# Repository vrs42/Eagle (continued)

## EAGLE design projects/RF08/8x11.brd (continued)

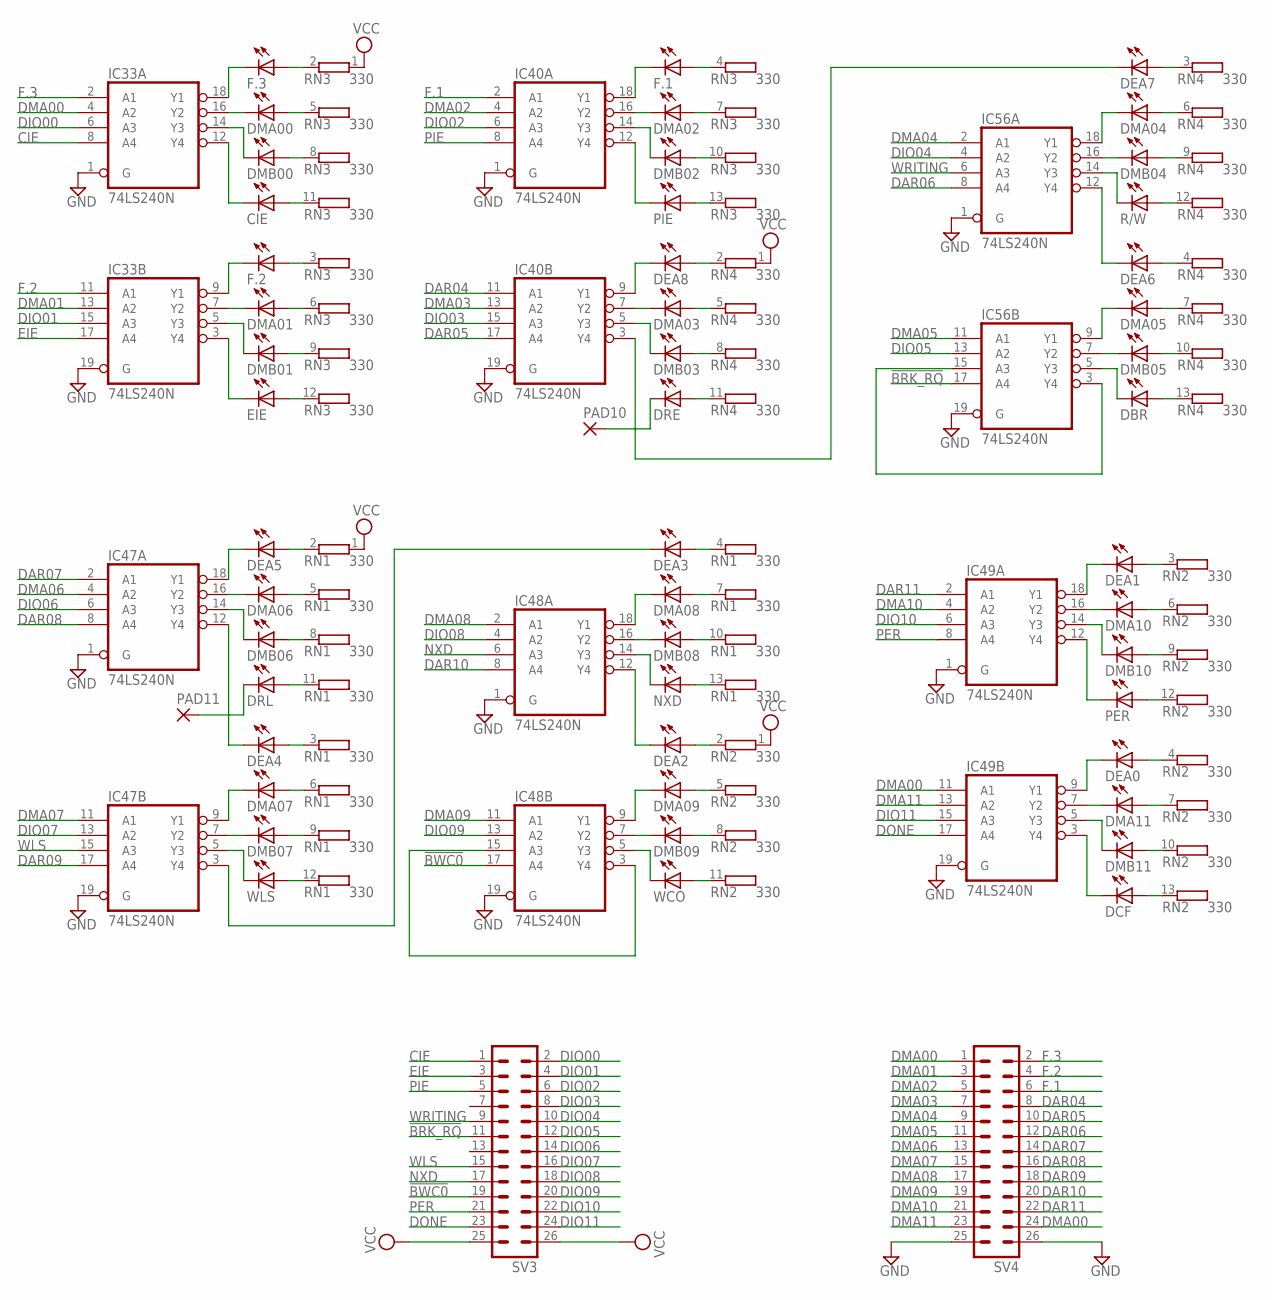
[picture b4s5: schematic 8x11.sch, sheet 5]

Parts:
CIE: LED5MM
DBR: LED5MM
DCF: LED5MM
DEA0, DEA1, DEA2, DEA3, DEA4, DEA5, DEA6, DEA7, DEA8: LED5MM
DMA00, DMA01, DMA02, DMA03, DMA04, DMA05, DMA06, DMA07, DMA08, DMA09, DMA10, DMA11: LED5MM
DMB00, DMB01, DMB02, DMB03, DMB04, DMB05, DMB06, DMB07, DMB08, DMB09, DMB10, DMB11: LED5MM
DRE: LED5MM
DRL: LED5MM
EIE: LED5MM
F.1, F.2, F.3: LED5MM
IC33, IC40, IC47, IC48, IC49, IC56: 74LS240N; DIL20
NXD: LED5MM
PAD10, PAD11: 1,6/0,8
PER: LED5MM
PIE: LED5MM
R/W: LED5MM
RN1, RN2, RN3, RN4: 330; SIL13
SV3, SV4: MA13-2
WCO: LED5MM
WLS: LED5MM

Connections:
!BRK_RQ: IC56.17 (A4), SV3.11; also elsewhere on the board
!BWC0: IC48.17 (A4), SV3.19; also elsewhere on the board
CIE: IC33.8 (A4), SV3.1; also elsewhere on the board
DAR04: IC40.11 (A1), SV4.8; also elsewhere on the board
DAR05: IC40.17 (A4), SV4.10; also elsewhere on the board
DAR06: IC56.8 (A4), SV4.12; also elsewhere on the board
DAR07: IC47.2 (A1), SV4.14; also elsewhere on the board
DAR08: IC47.8 (A4), SV4.16; also elsewhere on the board
DAR09: IC47.17 (A4), SV4.18; also elsewhere on the board
DAR10: IC48.8 (A4), SV4.20; also elsewhere on the board
DAR11: IC49.2 (A1), SV4.22; also elsewhere on the board
DIO00: IC33.6 (A3), SV3.2; also elsewhere on the board
DIO01: IC33.15 (A3), SV3.4; also elsewhere on the board
DIO02: IC40.6 (A3), SV3.6; also elsewhere on the board
DIO03: IC40.15 (A3), SV3.8; also elsewhere on the board
DIO04: IC56.4 (A2), SV3.10; also elsewhere on the board
DIO05: IC56.13 (A2), SV3.12; also elsewhere on the board
DIO06: IC47.6 (A3), SV3.14; also elsewhere on the board
DIO07: IC47.13 (A2), SV3.16; also elsewhere on the board
DIO08: IC48.4 (A2), SV3.18; also elsewhere on the board
DIO09: IC48.13 (A2), SV3.20; also elsewhere on the board
DIO10: IC49.6 (A3), SV3.22; also elsewhere on the board
DIO11: IC49.15 (A3), SV3.24; also elsewhere on the board
DMA00: IC33.4 (A2), IC49.11 (A1), SV4.1, SV4.24; also elsewhere on the board
DMA01: IC33.13 (A2), SV4.3; also elsewhere on the board
DMA02: IC40.4 (A2), SV4.5; also elsewhere on the board
DMA03: IC40.13 (A2), SV4.7; also elsewhere on the board
DMA04: IC56.2 (A1), SV4.9; also elsewhere on the board
DMA05: IC56.11 (A1), SV4.11; also elsewhere on the board
DMA06: IC47.4 (A2), SV4.13; also elsewhere on the board
DMA07: IC47.11 (A1), SV4.15; also elsewhere on the board
DMA08: IC48.2 (A1), SV4.17; also elsewhere on the board
DMA09: IC48.11 (A1), SV4.19; also elsewhere on the board
DMA10: IC49.4 (A2), SV4.21; also elsewhere on the board
DMA11: IC49.13 (A2), SV4.23; also elsewhere on the board
DONE: IC49.17 (A4), SV3.23; also elsewhere on the board
EIE: IC33.17 (A4), SV3.3; also elsewhere on the board
F.1: IC40.2 (A1), SV4.6; also elsewhere on the board
F.2: IC33.11 (A1), SV4.4; also elsewhere on the board
F.3: IC33.2 (A1), SV4.2; also elsewhere on the board
GND: IC33.1 (G), IC33.10 (GND), IC33.19 (G), IC40.1 (G), IC40.10 (GND), IC40.19 (G), IC47.1 (G), IC47.10 (GND), IC47.19 (G), IC48.1 (G), IC48.10 (GND), IC48.19 (G), IC49.1 (G), IC49.10 (GND), IC49.19 (G), IC56.1 (G), IC56.10 (GND), IC56.19 (G), SV4.25, SV4.26; also elsewhere on the board
unnamed: F.3.A, RN3.2
unnamed: F.2.A, RN3.3 (2)
unnamed: F.1.A, RN3.4 (2)
unnamed: DEA8.A, RN4.2
unnamed: DEA2.A, RN2.2
unnamed: DEA1.A, RN2.3 (2)
unnamed: DEA5.A, RN1.2
unnamed: DEA4.A, RN1.3 (2)
unnamed: DEA3.A, RN1.4 (2)
unnamed: DEA0.A, RN2.4 (2)
unnamed: DMA09.A, RN2.5 (2)
unnamed: DMA10.A, RN2.6 (2)
unnamed: DMA00.A, RN3.5 (2)
unnamed: DMA01.A, RN3.6 (2)
unnamed: DMA02.A, RN3.7 (2)
unnamed: DEA7.A, RN4.3 (2)
unnamed: DEA6.A, RN4.4 (2)
unnamed: DMA03.A, RN4.5 (2)
unnamed: DMA07.A, RN1.6 (2)
unnamed: DMA06.A, RN1.5 (2)
unnamed: DMA08.A, RN1.7 (2)
unnamed: DMA11.A, RN2.7 (2)
unnamed: DMB09.A, RN2.8 (2)
unnamed: DMB10.A, RN2.9 (2)
unnamed: PIE.A, RN3.13 (2)
unnamed: EIE.A, RN3.12 (2)
unnamed: CIE.A, RN3.11 (2)
unnamed: DMA04.A, RN4.6 (2)
unnamed: DMA05.A, RN4.7 (2)
unnamed: DMB03.A, RN4.8 (2)
unnamed: DMB06.A, RN1.8 (2)
unnamed: DMB07.A, RN1.9 (2)
unnamed: DMB08.A, RN1.10 (2)
unnamed: DMB11.A, RN2.10 (2)
unnamed: RN2.11 (2), WCO.A
unnamed: PER.A, RN2.12 (2)
unnamed: DMB02.A, RN3.10 (2)
unnamed: DMB01.A, RN3.9 (2)
unnamed: DMB00.A, RN3.8 (2)
unnamed: DRE.A, RN4.11 (2)
unnamed: R/W.A, RN4.12 (2)
unnamed: DBR.A, RN4.13 (2)
unnamed: DRL.A, RN1.11 (2)
unnamed: RN1.12 (2), WLS.A
unnamed: NXD.A, RN1.13 (2)
unnamed: DCF.A, RN2.13 (2)
unnamed: DMA09.K (C), IC48.9 (Y1)
unnamed: DMB09.K (C), IC48.7 (Y2)
unnamed: F.3.K (C), IC33.18 (Y1)
unnamed: DMA00.K (C), IC33.16 (Y2)
unnamed: CIE.K (C), IC33.12 (Y4)
unnamed: DMB00.K (C), IC33.14 (Y3)
unnamed: DMA01.K (C), IC33.7 (Y2)
unnamed: F.2.K (C), IC33.9 (Y1)
unnamed: DMB01.K (C), IC33.5 (Y3)
unnamed: EIE.K (C), IC33.3 (Y4)
unnamed: F.1.K (C), IC40.18 (Y1)
unnamed: DMA02.K (C), IC40.16 (Y2)
unnamed: DMB02.K (C), IC40.14 (Y3)
unnamed: IC40.12 (Y4), PIE.K (C)
unnamed: DMB03.K (C), IC40.5 (Y3)
unnamed: DMA03.K (C), IC40.7 (Y2)
unnamed: DEA8.K (C), IC40.9 (Y1)
unnamed: DEA7.K (C), IC40.3 (Y4)
unnamed: DMA04.K (C), IC56.18 (Y1)
unnamed: DMB04.K (C), IC56.16 (Y2)
unnamed: IC56.14 (Y3), R/W.K (C)
unnamed: DMB05.K (C), IC56.7 (Y2)
unnamed: DEA6.K (C), IC56.12 (Y4)
unnamed: DBR.K (C), IC56.5 (Y3)
unnamed: DMA06.K (C), IC47.16 (Y2)
unnamed: DEA4.K (C), IC47.12 (Y4)
unnamed: DMB07.K (C), IC47.7 (Y2)
unnamed: DEA5.K (C), IC47.18 (Y1)
unnamed: DMA07.K (C), IC47.9 (Y1)
unnamed: IC47.5 (Y3), WLS.K (C)
unnamed: DMB06.K (C), IC47.14 (Y3)
unnamed: DEA3.K (C), IC47.3 (Y4)
unnamed: DMA08.K (C), IC48.18 (Y1)
unnamed: DMB08.K (C), IC48.16 (Y2)
unnamed: IC48.14 (Y3), NXD.K (C)
unnamed: IC48.5 (Y3), WCO.K (C)
unnamed: IC49.12 (Y4), PER.K (C)
unnamed: DMB10.K (C), IC49.14 (Y3)
unnamed: DEA2.K (C), IC48.12 (Y4)
unnamed: DMA10.K (C), IC49.16 (Y2)
unnamed: DEA1.K (C), IC49.18 (Y1)
unnamed: IC48.3 (Y4), IC48.15 (A3)
unnamed: DMA11.K (C), IC49.7 (Y2)
unnamed: DEA0.K (C), IC49.9 (Y1)
unnamed: DMB11.K (C), IC49.5 (Y3)
unnamed: DCF.K (C), IC49.3 (Y4)
unnamed: DRE.K (C), PAD10.1
unnamed: DRL.K (C), PAD11.1
unnamed: DMA05.K (C), IC56.9 (Y1)
unnamed: DMB04.A, RN4.9 (2)
unnamed: DMB05.A, RN4.10 (2)
unnamed: IC56.3 (Y4), IC56.15 (A3)
NXD: IC48.6 (A3), SV3.17; also elsewhere on the board
PER: IC49.8 (A4), SV3.21; also elsewhere on the board
PIE: IC40.8 (A4), SV3.5; also elsewhere on the board
VCC: IC33.20 (VCC), IC40.20 (VCC), IC47.20 (VCC), IC48.20 (VCC), IC49.20 (VCC), IC56.20 (VCC), RN1.1, RN2.1, RN3.1, RN4.1, SV3.25, SV3.26; also elsewhere on the board
WLS: IC47.15 (A3), SV3.15; also elsewhere on the board
WRITING: IC56.6 (A3), SV3.9; also elsewhere on the board

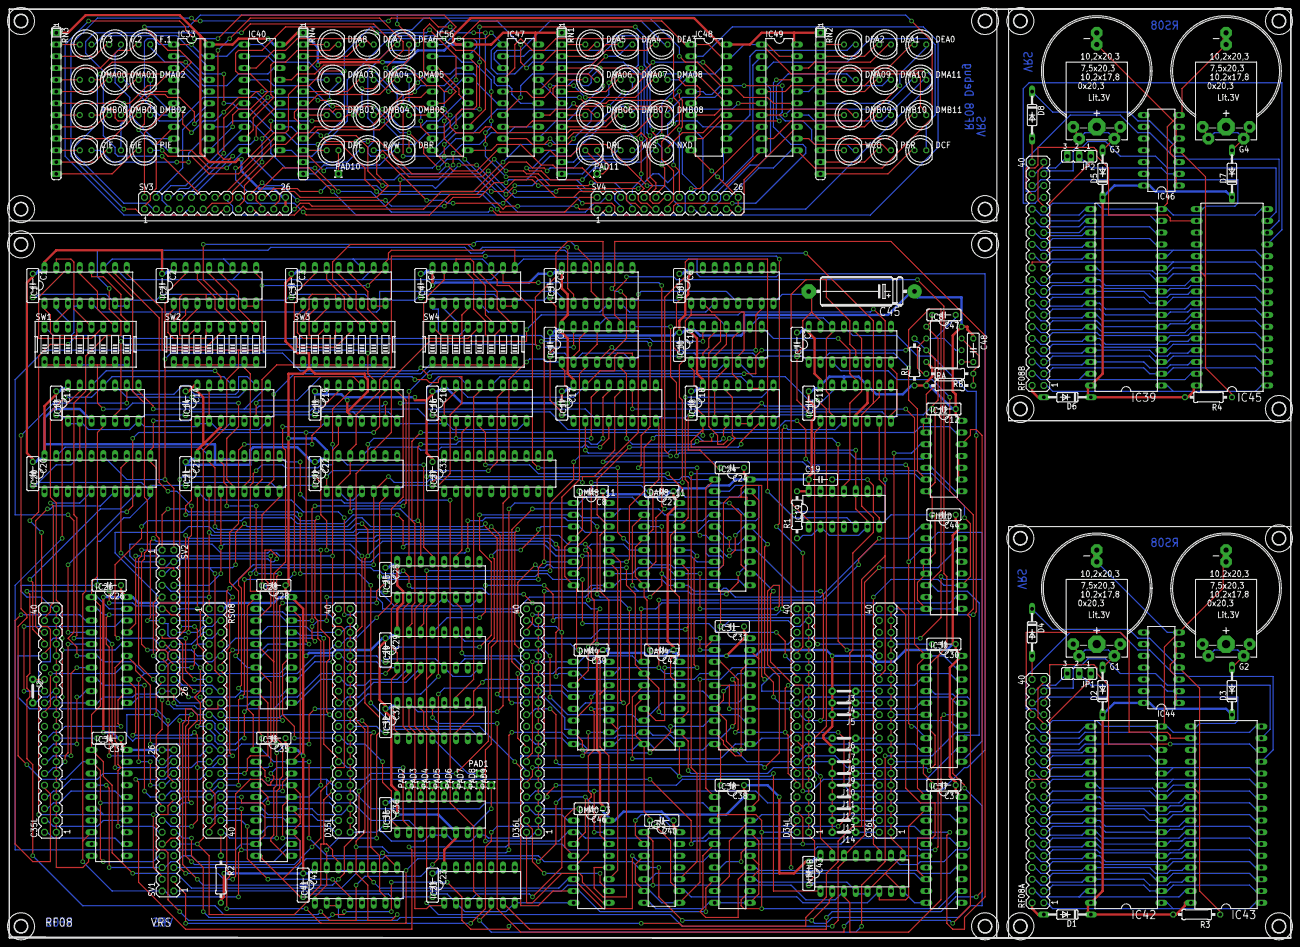
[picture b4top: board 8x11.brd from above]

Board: 2 copper layers, 276.9 x 200.7 mm, 236 parts (0 on the bottom side), 335 nets.

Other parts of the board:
U$1, U$2, U$3, U$4, U$5, U$6, U$7, U$8, U$9, U$10, U$11, U$12, U$13, U$14, U$16, U$17: 2,8
U$18: SIERRA-PROTO

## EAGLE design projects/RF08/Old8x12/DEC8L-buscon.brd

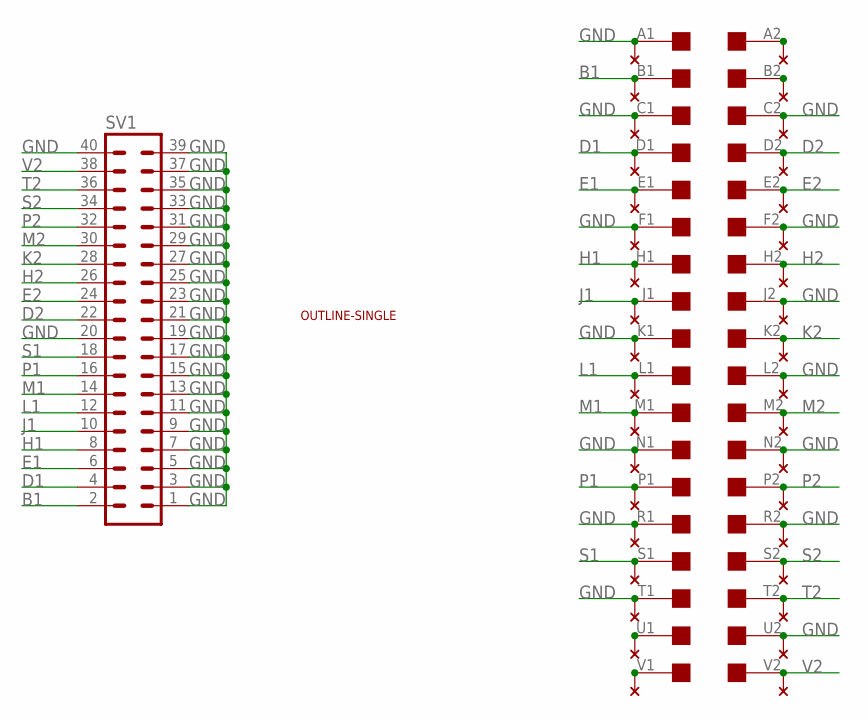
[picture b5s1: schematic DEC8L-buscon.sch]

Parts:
EDGE1: EDGE-2CONNECTOR; EDGE-CON2
SV1: MA20-2
U$4: OUTLINE-SINGLE; SINGLE
U$5: THRU-HOLE2; THRU-HOLEB

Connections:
B1: EDGE1.B1, SV1.2, U$5.B1
D1: EDGE1.D1, SV1.4, U$5.D1
D2: EDGE1.D2, SV1.22, U$5.D2
E1: EDGE1.E1, SV1.6, U$5.E1
E2: EDGE1.E2, SV1.24, U$5.E2
GND: EDGE1.A1, EDGE1.C1, EDGE1.C2, EDGE1.F1, EDGE1.F2, EDGE1.J2, EDGE1.K1, EDGE1.L2, EDGE1.N1, EDGE1.N2, EDGE1.R1, EDGE1.R2, EDGE1.T1, EDGE1.U2, SV1.1, SV1.3, SV1.5, SV1.7, SV1.9, SV1.11, SV1.13, SV1.15, SV1.17, SV1.19, SV1.20, SV1.21, SV1.23, SV1.25, SV1.27, SV1.29, SV1.31, SV1.33, SV1.35, SV1.37, SV1.39, SV1.40, U$5.A1, U$5.C1, U$5.C2, U$5.F1, U$5.F2, U$5.J2, U$5.K1, U$5.L2, U$5.N1, U$5.N2, U$5.R1, U$5.R2, U$5.T1, U$5.U2
H1: EDGE1.H1, SV1.8, U$5.H1
H2: EDGE1.H2, SV1.26, U$5.H2
J1: EDGE1.J1, SV1.10, U$5.J1
K2: EDGE1.K2, SV1.28, U$5.K2
L1: EDGE1.L1, SV1.12, U$5.L1
M1: EDGE1.M1, SV1.14, U$5.M1
M2: EDGE1.M2, SV1.30, U$5.M2
unnamed: EDGE1.B2, U$5.B2
unnamed: EDGE1.A2, U$5.A2
unnamed: EDGE1.U1, U$5.U1
unnamed: EDGE1.V1, U$5.V1
P1: EDGE1.P1, SV1.16, U$5.P1
P2: EDGE1.P2, SV1.32, U$5.P2
S1: EDGE1.S1, SV1.18, U$5.S1
S2: EDGE1.S2, SV1.34, U$5.S2
T2: EDGE1.T2, SV1.36, U$5.T2
V2: EDGE1.V2, SV1.38, U$5.V2

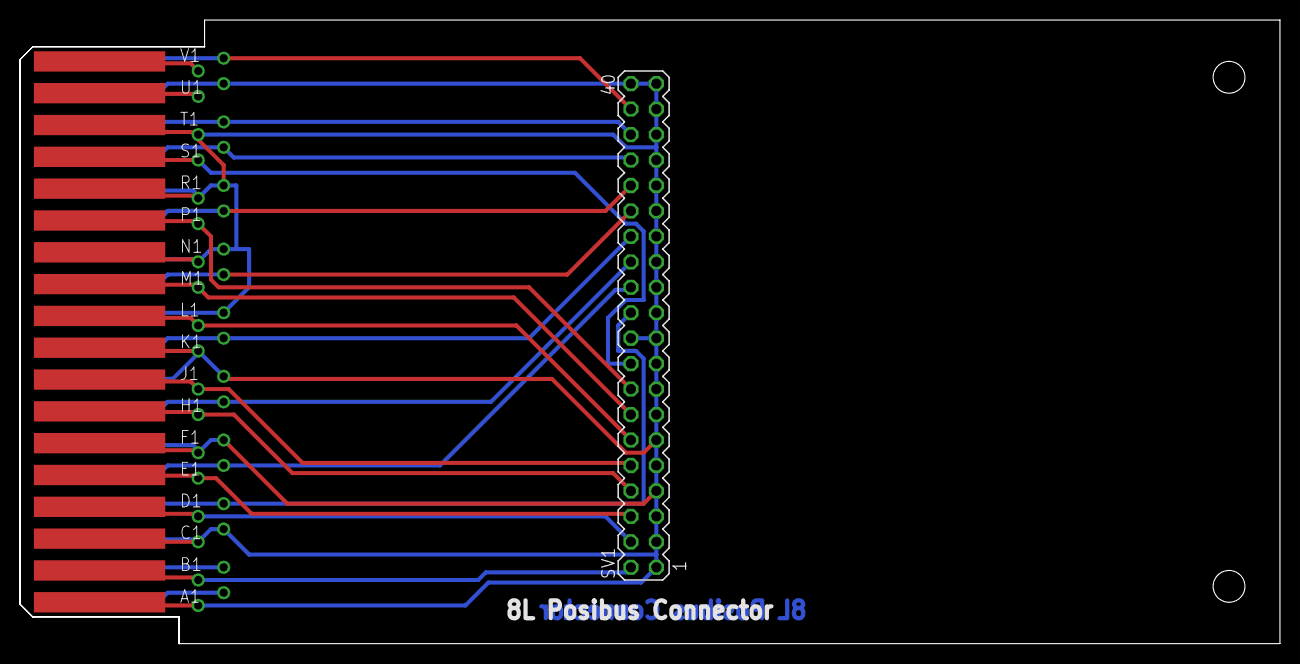
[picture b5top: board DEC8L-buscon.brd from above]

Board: 2 copper layers, 125.7 x 62.2 mm, 4 parts (0 on the bottom side), 23 nets.

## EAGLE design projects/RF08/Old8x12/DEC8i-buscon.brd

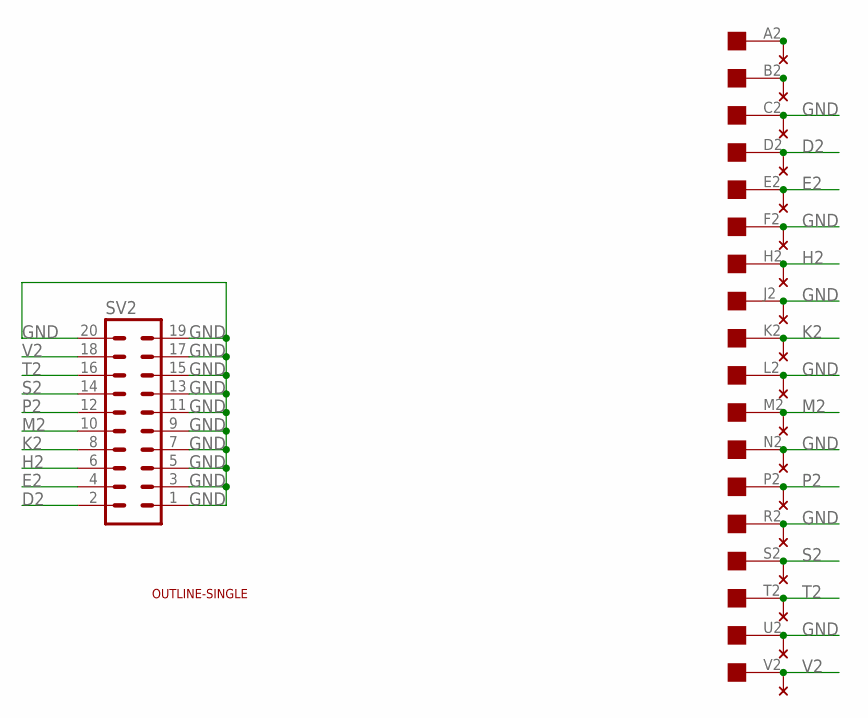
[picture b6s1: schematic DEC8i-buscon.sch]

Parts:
SV2: MA10-2
U$4: EDGE-1; EDGE-CON1
U$5: THRU-HOLE1
U$6: OUTLINE-SINGLE; SINGLE

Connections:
D2: SV2.2, U$4.D2, U$5.D2
E2: SV2.4, U$4.E2, U$5.E2
GND: SV2.1, SV2.3, SV2.5, SV2.7, SV2.9, SV2.11, SV2.13, SV2.15, SV2.17, SV2.19, SV2.20, U$4.C2, U$4.F2, U$4.J2, U$4.L2, U$4.N2, U$4.R2, U$4.U2, U$5.C2, U$5.F2, U$5.J2, U$5.L2, U$5.N2, U$5.R2, U$5.U2
H2: SV2.6, U$4.H2, U$5.H2
K2: SV2.8, U$4.K2, U$5.K2
M2: SV2.10, U$4.M2, U$5.M2
unnamed: U$4.B2, U$5.B2
unnamed: U$4.A2, U$5.A2
P2: SV2.12, U$4.P2, U$5.P2
S2: SV2.14, U$4.S2, U$5.S2
T2: SV2.16, U$4.T2, U$5.T2
V2: SV2.18, U$4.V2, U$5.V2

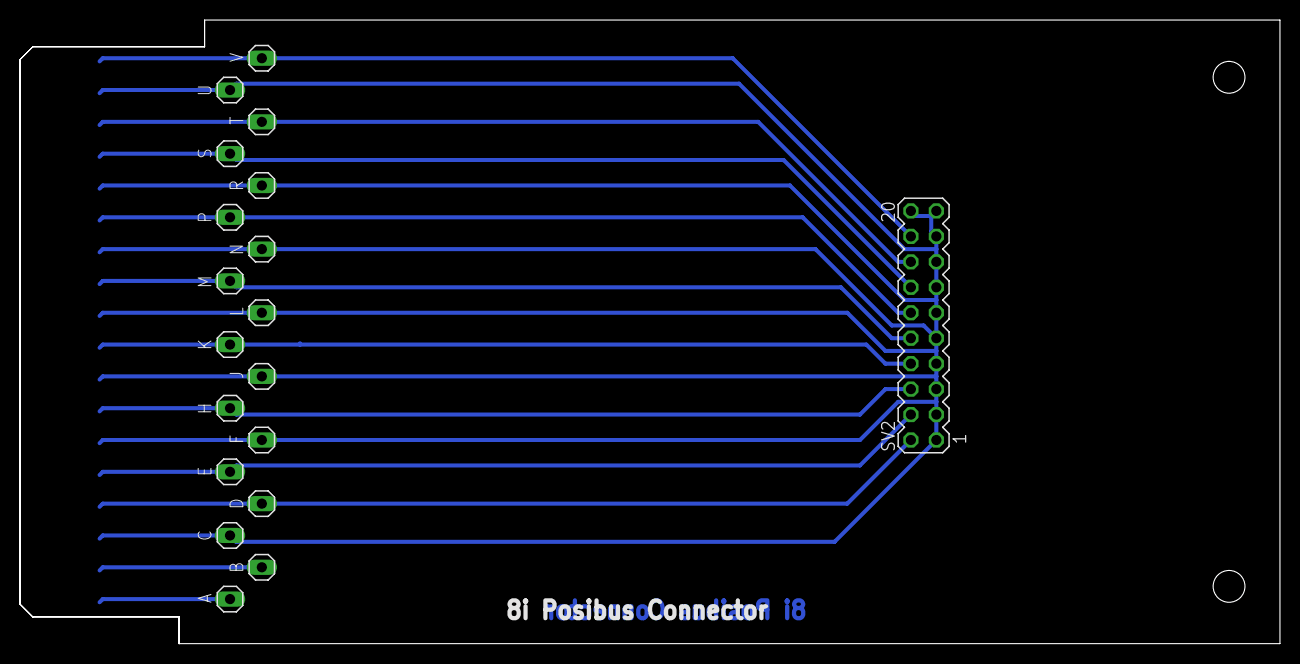
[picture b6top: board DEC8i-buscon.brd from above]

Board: 2 copper layers, 125.7 x 62.2 mm, 4 parts (0 on the bottom side), 12 nets.

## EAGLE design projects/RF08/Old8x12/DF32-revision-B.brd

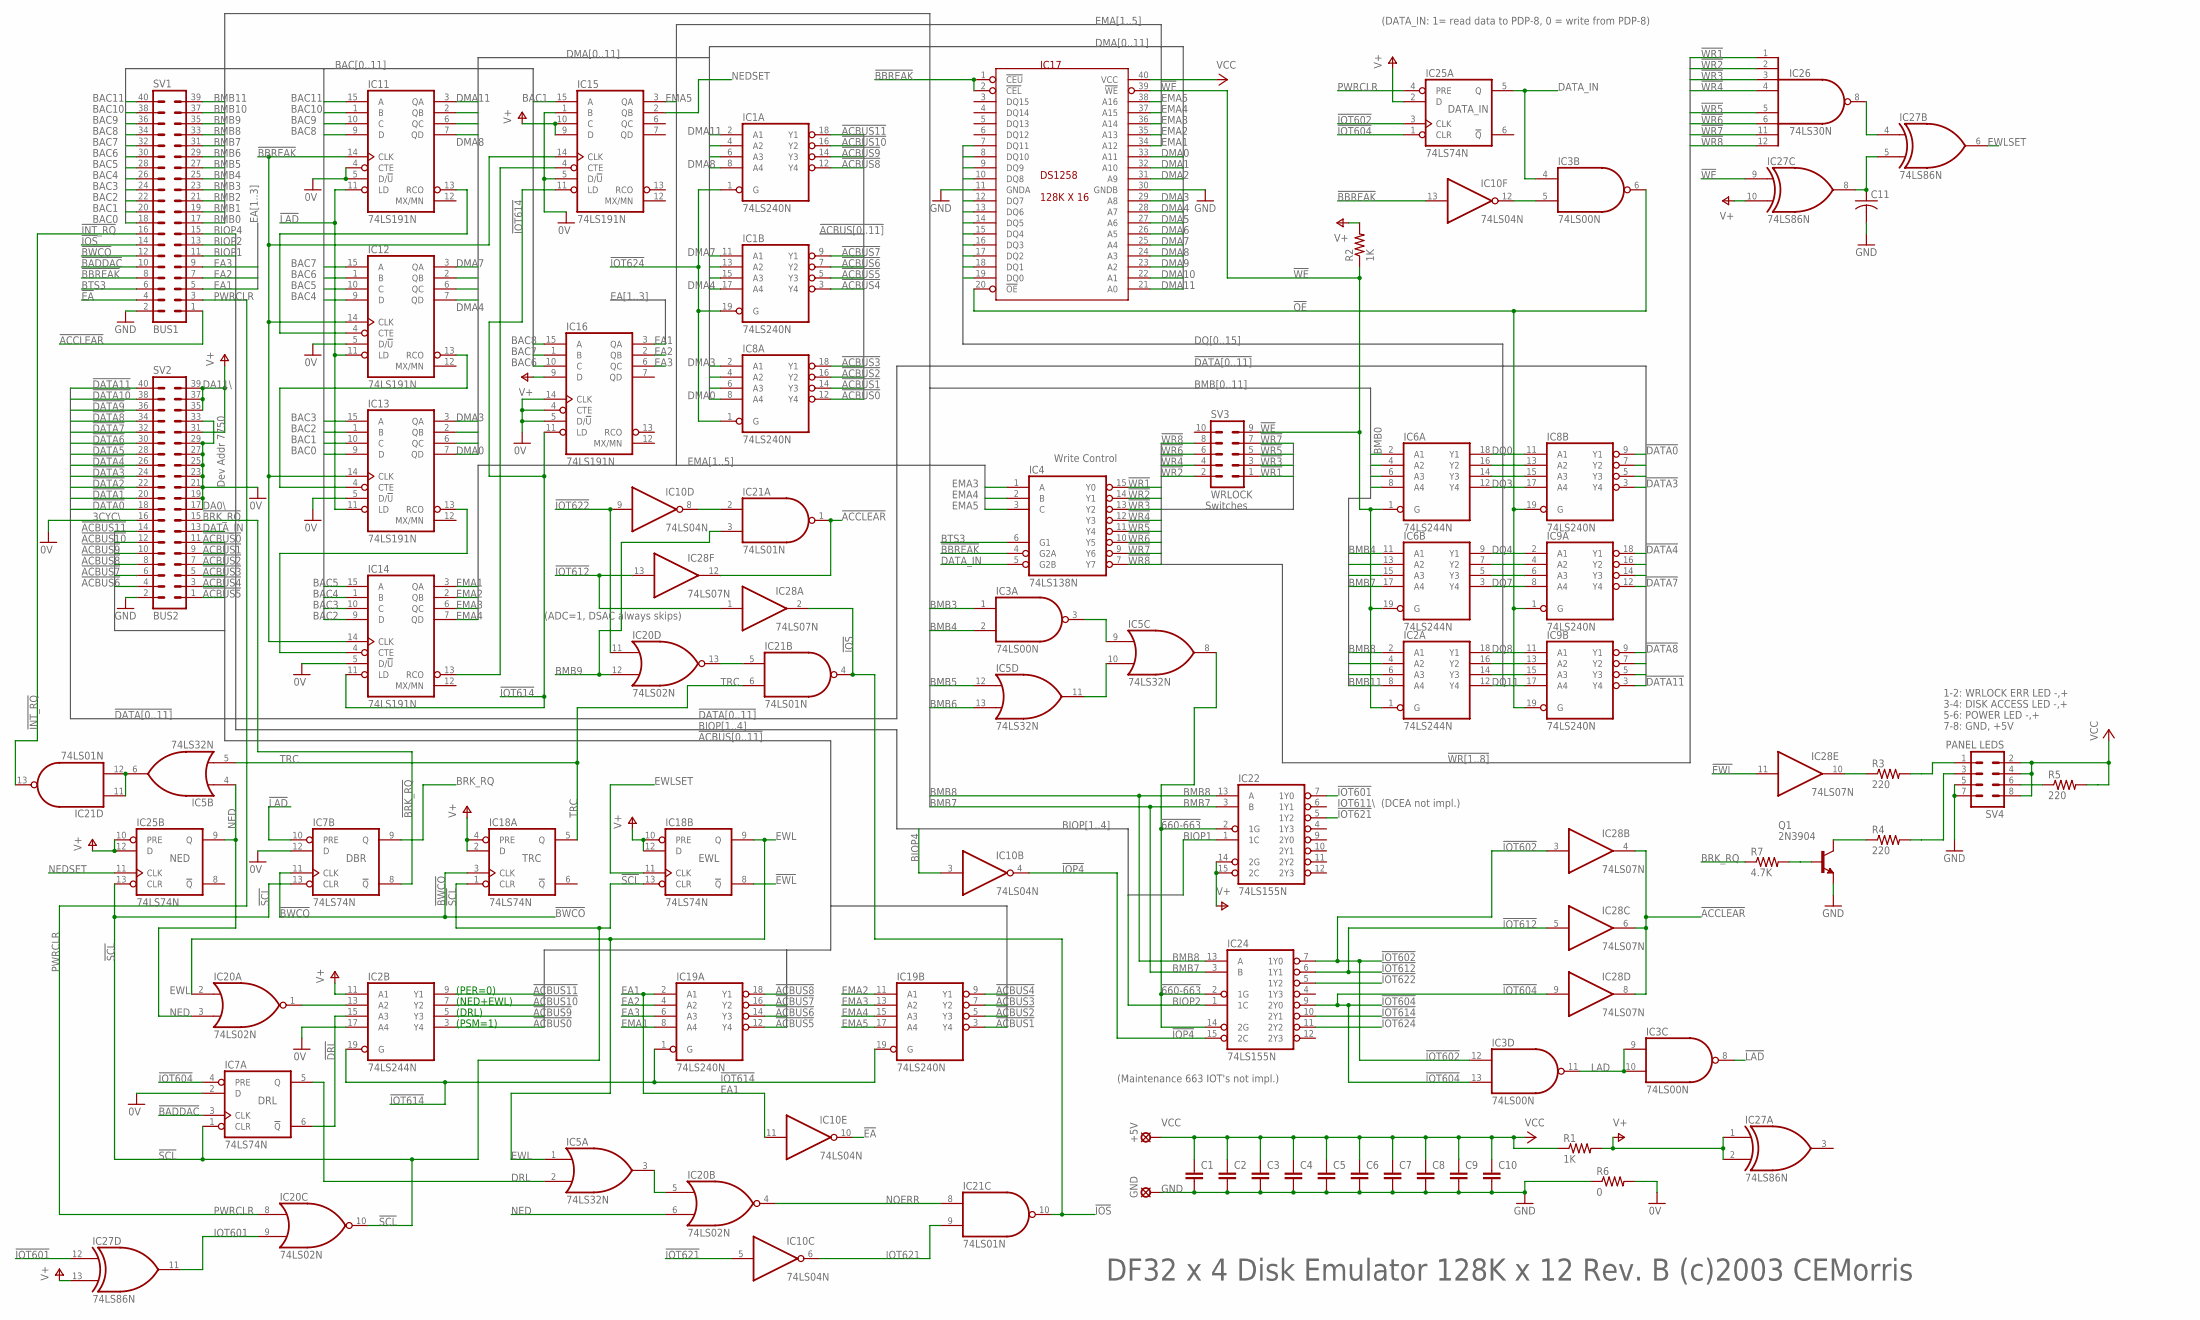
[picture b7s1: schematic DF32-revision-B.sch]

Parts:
+5V: SE14
C1, C2, C3, C4, C5, C6, C7, C8, C9, C10: C5/3.5; C5B3.5
C11: C-US025-025X050; C025-025X050
GND: SE14
IC1, IC8, IC9, IC19: 74LS240N; DIL20
IC2, IC6: 74LS244N; DIL20
IC3: 74LS00N; DIL14
IC4: 74LS138N; DIL16
IC5: 74LS32N; DIL14
IC7, IC18, IC25: 74LS74N; DIL14
IC10: 74LS04N; DIL14
IC11, IC12, IC13, IC14, IC15, IC16: 74LS191N; DIL16
IC17: DS1258; DIL40
IC20: 74LS02N; DIL14
IC21: 74LS01N; DIL14
IC22, IC24: 74LS155N; DIL16
IC26: 74LS30N; DIL14
IC27: 74LS86N; DIL14
IC28: 74LS07N; DIL14
Q1: 2N3904; TO92
R1: 1K; 0204/5
R2: 1K; 0204/7
R3, R4, R5: 220; 0204/5
R6: 0; 0204/5
R7: 4.7K; 0204/5
SV1: BUS1; MA20-2
SV2: BUS2; MA20-2
SV3: WRLOCK; MA05-2
SV4: PANEL LEDS; MA04-2

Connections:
0V: IC2.17 (A4), IC7.2 (D), IC7.12 (D), IC11.4 (CTE), IC11.5 (D/!U), IC12.5 (D/!U), IC13.5 (D/!U), IC14.5 (D/!U), IC15.1 (B), IC15.5 (D/!U), IC16.4 (CTE), IC16.5 (D/!U), IC16.14 (CLK), R6.2, SV2.16, SV2.17, SV2.19, SV2.21, SV2.23, SV2.25, SV2.27, SV2.29, SV2.33
!660-663: IC5.8 (O), IC22.2 (1G), IC24.2 (1G), IC24.14 (2G)
!(NED+EWL): IC2.13 (A2), IC20.1 (O)
!ACBUS0: IC2.3 (Y4), IC8.12 (Y4), SV2.11
!ACBUS1: IC8.14 (Y3), IC19.3 (Y4), SV2.9
!ACBUS2: IC8.16 (Y2), IC19.5 (Y3), SV2.7
!ACBUS3: IC8.18 (Y1), IC19.7 (Y2), SV2.5
!ACBUS4: IC1.3 (Y4), IC19.9 (Y1), SV2.3
!ACBUS5: IC1.5 (Y3), IC19.12 (Y4), SV2.1
!ACBUS6: IC1.7 (Y2), IC19.14 (Y3), SV2.4
!ACBUS7: IC1.9 (Y1), IC19.16 (Y2), SV2.6
!ACBUS8: IC1.12 (Y4), IC19.18 (Y1), SV2.8
!ACBUS9: IC1.14 (Y3), IC2.5 (Y3), SV2.10
!ACBUS10: IC1.16 (Y2), IC2.7 (Y2), SV2.12
!ACBUS11: IC1.18 (Y1), IC2.9 (Y1), SV2.14
!ACCLEAR: IC21.1 (O), IC28.4 (O), IC28.6 (O), IC28.8 (O), IC28.12 (O), SV1.1
!BADDAC: IC7.3 (CLK), SV1.10
!BBREAK: IC4.4 (G2A), IC10.13 (I), IC11.14 (CLK), IC12.14 (CLK), IC13.14 (CLK), IC14.14 (CLK), IC15.14 (CLK), IC17.1 (!CEU), IC17.2 (!CEL), SV1.8
!BRK_RQ: IC7.8 (!Q), SV2.15
!BWCO: IC7.11 (CLK), IC18.3 (CLK), SV1.12
!DATA0: IC8.9 (Y1), SV2.18
!DATA1: IC8.7 (Y2), SV2.20
!DATA2: IC8.5 (Y3), SV2.22
!DATA3: IC8.3 (Y4), SV2.24
!DATA4: IC9.18 (Y1), SV2.26
!DATA5: IC9.16 (Y2), SV2.28
!DATA6: IC9.14 (Y3), SV2.30
!DATA7: IC9.12 (Y4), SV2.32
!DATA8: IC9.9 (Y1), SV2.34
!DATA9: IC9.7 (Y2), SV2.36
!DATA10: IC9.5 (Y3), SV2.38
!DATA11: IC9.3 (Y4), SV2.40
!DRL: IC2.15 (A3), IC7.6 (!Q)
!EA: IC10.10 (O), SV1.4
!EWL: IC18.8 (!Q), IC28.11 (I)
!INT_RQ: IC21.13 (O), SV1.16
!IOP4: IC10.4 (O), IC24.15 (2C)
!IOS: IC21.4 (O), IC21.10 (O), IC28.2 (O), SV1.14
!IOT601: IC22.7 (1Y0), IC27.12 (I0)
!IOT602: IC3.12 (I0), IC24.7 (1Y0), IC25.3 (CLK), IC28.3 (I)
!IOT604: IC3.13 (I1), IC7.4 (PRE), IC24.9 (2Y0), IC25.1 (CLR), IC28.9 (I)
!IOT612: IC24.6 (1Y1), IC28.1 (I), IC28.5 (I), IC28.13 (I)
!IOT614: IC2.19 (G), IC14.11 (LD), IC15.11 (LD), IC16.11 (LD), IC19.1 (G), IC19.19 (G), IC24.10 (2Y1)
!IOT621: IC10.5 (I), IC22.5 (1Y2)
!IOT622: IC10.9 (I), IC20.11 (I0), IC24.5 (1Y2)
!IOT624: IC1.1 (G), IC1.19 (G), IC8.1 (G), IC24.11 (2Y2)
!LAD: IC3.8 (O), IC7.10 (PRE), IC11.11 (LD), IC12.11 (LD), IC13.11 (LD)
!OE: IC3.6 (O), IC8.19 (G), IC9.1 (G), IC9.19 (G), IC17.20 (!OE)
!SCL: IC7.1 (CLR), IC7.13 (CLR), IC18.1 (CLR), IC18.13 (CLR), IC20.10 (O), IC25.13 (CLR)
!WE: IC2.1 (G), IC6.1 (G), IC6.19 (G), IC17.39 (!WE), IC27.9 (I0), R2.1, SV3.9
!WR1: IC4.15 (Y0), IC26.1 (I0), SV3.1
!WR2: IC4.14 (Y1), IC26.2 (I1), SV3.2
!WR3: IC4.13 (Y2), IC26.3 (I2), SV3.3
!WR4: IC4.12 (Y3), IC26.4 (I3), SV3.4
!WR5: IC4.11 (Y4), IC26.5 (I4), SV3.5
!WR6: IC4.10 (Y5), IC26.6 (I5), SV3.6
!WR7: IC4.9 (Y6), IC26.11 (I6), SV3.7
!WR8: IC4.7 (Y7), IC26.12 (I7), SV3.8
BAC0: IC13.9 (D), SV1.18
BAC1: IC13.10 (C), IC15.15 (A), SV1.20
BAC2: IC13.1 (B), IC14.9 (D), SV1.22
BAC3: IC13.15 (A), IC14.10 (C), SV1.24
BAC4: IC12.9 (D), IC14.1 (B), SV1.26
BAC5: IC12.10 (C), IC14.15 (A), SV1.28
BAC6: IC12.1 (B), IC16.10 (C), SV1.30
BAC7: IC12.15 (A), IC16.1 (B), SV1.32
BAC8: IC11.9 (D), IC16.15 (A), SV1.34
BAC9: IC11.10 (C), SV1.36
BAC10: IC11.1 (B), SV1.38
BAC11: IC11.15 (A), SV1.40
BIOP1: IC22.1 (1C), SV1.11
BIOP2: IC24.1 (1C), SV1.13
BIOP4: IC10.3 (I), SV1.15
BMB0: IC6.2 (A1), SV1.17
BMB1: IC6.4 (A2), SV1.19
BMB2: IC6.6 (A3), SV1.21
BMB3: IC3.1 (I0), IC6.8 (A4), SV1.23
BMB4: IC3.2 (I1), IC6.11 (A1), SV1.25
BMB5: IC5.12 (I0), IC6.13 (A2), SV1.27
BMB6: IC5.13 (I1), IC6.15 (A3), SV1.29
BMB7: IC6.17 (A4), IC22.3 (B), IC24.3 (B), SV1.31
BMB8: IC2.2 (A1), IC22.13 (A), IC24.13 (A), SV1.33
BMB9: IC2.4 (A2), IC20.12 (I1), IC21.3 (I1), SV1.35
BMB10: IC2.6 (A3), SV1.37
BMB11: IC2.8 (A4), SV1.39
BRK_RQ: IC7.9 (Q), R7.1
BTS3: IC4.6 (G1), SV1.6
DATA_IN: IC3.4 (I0), IC4.5 (G2B), IC25.5 (Q), SV2.13
DISK_LED: R4.2, SV4.3
DMA0: IC8.8 (A4), IC13.7 (QD), IC17.33 (A11)
DMA1: IC8.6 (A3), IC13.6 (QC), IC17.32 (A10)
DMA2: IC8.4 (A2), IC13.2 (QB), IC17.31 (A9)
DMA3: IC8.2 (A1), IC13.3 (QA), IC17.29 (A8)
DMA4: IC1.17 (A4), IC12.7 (QD), IC17.28 (A7)
DMA5: IC1.15 (A3), IC12.6 (QC), IC17.27 (A6)
DMA6: IC1.13 (A2), IC12.2 (QB), IC17.26 (A5)
DMA7: IC1.11 (A1), IC12.3 (QA), IC17.25 (A4)
DMA8: IC1.8 (A4), IC11.7 (QD), IC17.24 (A3)
DMA9: IC1.6 (A3), IC11.6 (QC), IC17.23 (A2)
DMA10: IC1.4 (A2), IC11.2 (QB), IC17.22 (A1)
DMA11: IC1.2 (A1), IC11.3 (QA), IC17.21 (A0)
DQ0: IC6.18 (Y1), IC8.11 (A1), IC17.19 (DQ0)
DQ1: IC6.16 (Y2), IC8.13 (A2), IC17.18 (DQ1)
DQ2: IC6.14 (Y3), IC8.15 (A3), IC17.17 (DQ2)
DQ3: IC6.12 (Y4), IC8.17 (A4), IC17.16 (DQ3)
DQ4: IC6.9 (Y1), IC9.2 (A1), IC17.15 (DQ4)
DQ5: IC6.7 (Y2), IC9.4 (A2), IC17.14 (DQ5)
DQ6: IC6.5 (Y3), IC9.6 (A3), IC17.13 (DQ6)
DQ7: IC6.3 (Y4), IC9.8 (A4), IC17.12 (DQ7)
DQ8: IC2.18 (Y1), IC9.11 (A1), IC17.10 (DQ8)
DQ9: IC2.16 (Y2), IC9.13 (A2), IC17.9 (DQ9)
DQ10: IC2.14 (Y3), IC9.15 (A3), IC17.8 (DQ10)
DQ11: IC2.12 (Y4), IC9.17 (A4), IC17.7 (DQ11)
DRL: IC5.2 (I1), IC7.5 (Q)
EA1: IC10.11 (I), IC16.3 (QA), IC19.2 (A1), SV1.5
EA2: IC16.2 (QB), IC19.4 (A2), SV1.7
EA3: IC16.6 (QC), IC19.6 (A3), SV1.9
EMA1: IC14.3 (QA), IC17.34 (A12), IC19.8 (A4)
EMA2: IC14.2 (QB), IC17.35 (A13), IC19.11 (A1)
EMA3: IC4.1 (A), IC14.6 (QC), IC17.36 (A14), IC19.13 (A2)
EMA4: IC4.2 (B), IC14.7 (QD), IC17.37 (A15), IC19.15 (A3)
EMA5: IC4.3 (C), IC15.3 (QA), IC17.38 (A16), IC19.17 (A4)
EWL: IC5.1 (I0), IC18.9 (Q), IC20.2 (I0)
EWLSET: IC18.11 (CLK), IC27.6 (O)
GND: C1.2, C2.2, C3.2, C4.2, C5.2, C6.2, C7.2, C8.2, C9.2, C10.2, C11.2, GND.MP, IC1.10 (GND), IC2.10 (GND), IC3.7 (GND), IC4.8 (GND), IC5.7 (GND), IC6.10 (GND), IC7.7 (GND), IC8.10 (GND), IC9.10 (GND), IC10.7 (GND), IC11.8 (GND), IC12.8 (GND), IC13.8 (GND), IC14.8 (GND), IC15.8 (GND), IC16.8 (GND), IC17.11 (GNDA), IC17.30 (GNDB), IC18.7 (GND), IC19.10 (GND), IC20.7 (GND), IC21.7 (GND), IC22.8 (GND), IC24.8 (GND), IC25.7 (GND), IC26.7 (GND), IC27.7 (GND), IC28.7 (GND), Q1.3 (E), R6.1, SV1.2, SV2.2, SV4.5, SV4.7
IOT601: IC20.9 (I1), IC27.11 (O)
IOT621: IC10.6 (O), IC21.9 (I1)
LAD: IC3.9 (I0), IC3.10 (I1), IC3.11 (O)
unnamed: C11.1, IC27.5 (I1), IC27.8 (O)
unnamed: IC5.6 (O), IC21.11 (I0), IC21.12 (I1)
unnamed: IC28.10 (O), R3.1
unnamed: IC3.5 (I1), IC10.12 (O)
unnamed: Q1.1 (C), R4.1
unnamed: R5.1, SV4.6
unnamed: IC13.13 (RCO), IC14.4 (CTE)
unnamed: IC12.13 (RCO), IC13.4 (CTE)
unnamed: IC11.13 (RCO), IC12.4 (CTE)
unnamed: IC3.3 (O), IC5.9 (I0)
unnamed: IC14.13 (RCO), IC15.4 (CTE)
unnamed: IC5.10 (I1), IC5.11 (O)
unnamed: IC20.13 (O), IC21.5 (I0)
unnamed: IC5.3 (O), IC20.5 (I0)
unnamed: IC10.8 (O), IC21.2 (I0)
unnamed: IC26.8 (O), IC27.4 (I0)
unnamed: Q1.2 (B), R7.2
NED: IC5.4 (I0), IC20.3 (I1), IC20.6 (I1), IC25.9 (Q)
NEDSET: IC15.2 (QB), IC25.11 (CLK)
NOERR: IC20.4 (O), IC21.8 (I0)
PWRCLR: IC20.8 (I0), IC25.4 (PRE), SV1.3
TRC: IC5.5 (I1), IC18.5 (Q), IC21.6 (I1)
V+: IC2.11 (A1), IC15.9 (D), IC15.10 (C), IC16.9 (D), IC18.2 (D), IC18.4 (PRE), IC18.10 (PRE), IC18.12 (D), IC22.14 (2G), IC22.15 (2C), IC25.2 (D), IC25.10 (PRE), IC25.12 (D), IC27.1 (I0), IC27.2 (I1), IC27.10 (I1), IC27.13 (I1), R1.2, R2.2, SV2.31, SV2.35, SV2.37, SV2.39
VCC: +5V.MP, C1.1, C2.1, C3.1, C4.1, C5.1, C6.1, C7.1, C8.1, C9.1, C10.1, IC1.20 (VCC), IC2.20 (VCC), IC3.14 (VCC), IC4.16 (VCC), IC5.14 (VCC), IC6.20 (VCC), IC7.14 (VCC), IC8.20 (VCC), IC9.20 (VCC), IC10.14 (VCC), IC11.16 (VCC), IC12.16 (VCC), IC13.16 (VCC), IC14.16 (VCC), IC15.16 (VCC), IC16.16 (VCC), IC17.40 (VCC), IC18.14 (VCC), IC19.20 (VCC), IC20.14 (VCC), IC21.14 (VCC), IC22.16 (VCC), IC24.16 (VCC), IC25.14 (VCC), IC26.14 (VCC), IC27.14 (VCC), IC28.14 (VCC), R1.1, R5.2, SV4.2, SV4.4, SV4.8
WRITELOCK_LED: R3.2, SV4.1

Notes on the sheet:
(PER=0)
DF32 x 4 Disk Emulator 128K x 12 Rev. B (c)2003 CEMorris
NED
DBR
TRC
EWL
IOT611\\ (DCEA not impl.)
(DATA_IN: 1= read data to PDP-8, 0 = write from PDP-8)
DRL
Dev Addr 7750
DA11\\
DA0\\
3CYC\\
DATA_IN
(PSM=1)
(NED+EWL)
(DRL)
(ADC=1, DSAC always skips)
Write Control
Switches
1-2: WRLOCK ERR LED -,+
3-4: DISK ACCESS LED -,+
5-6: POWER LED -,+
7-8: GND, +5V
(Maintenance 663 IOT's not impl.)

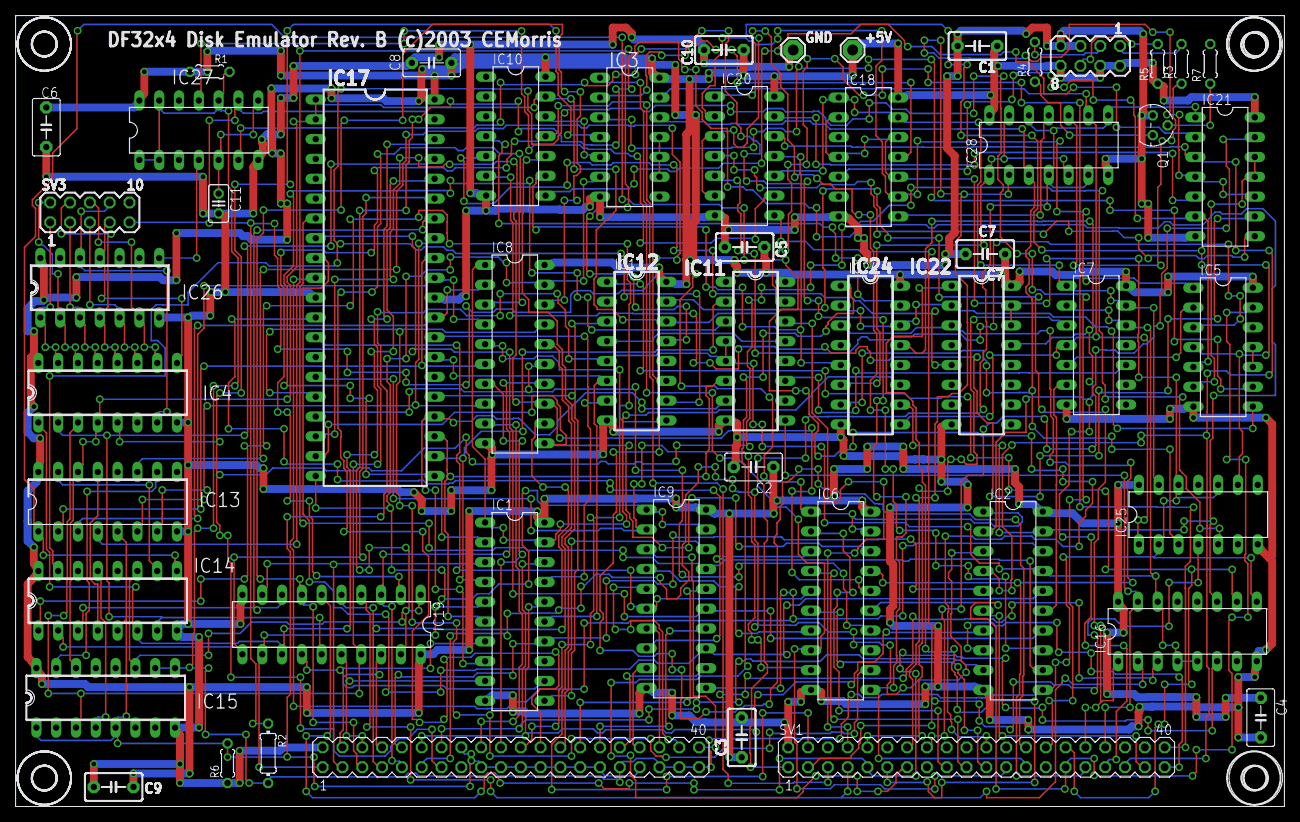
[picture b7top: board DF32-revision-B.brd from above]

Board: 2 copper layers, 162.7 x 101.4 mm, 56 parts (0 on the bottom side), 153 nets.

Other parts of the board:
U$1, U$2, U$3, U$4: 3,0
